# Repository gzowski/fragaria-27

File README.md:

# Fragaria-27
27 Key macropad with MX hotswap sockets, designed to fit within a iphone 13/14 pro max case giving many options given the amount of phone case options available.

* This is another project which has been possible thanks to the sponsorship from pcbway.com 

## Features
* 27 Key layout
* Per key RGB LED's
* Embedded RP2040 controller
* QMK Firmware with VIA support
* Fits into an iphone 13/14 Pro Max case
* 4 mounting screws for custom case designs

* Currently working on a one handed keyboard mode using chord

## Parts
| Part | Quantity     | Description                |
| :-------- | :------- | :------------------------- |
| Switches | 27 | MX Switches |
| Keycaps | 27 | 1U Keycaps |
| PCB Components | - | Included in kicad design and within PCB/bom/ibom.html |
## Optional Parts

| Part | Quantity     | Description                |
| :-------- | :------- | :------------------------- |
| Phone Case | 1 | iPhone 13/14 Pro Max case |

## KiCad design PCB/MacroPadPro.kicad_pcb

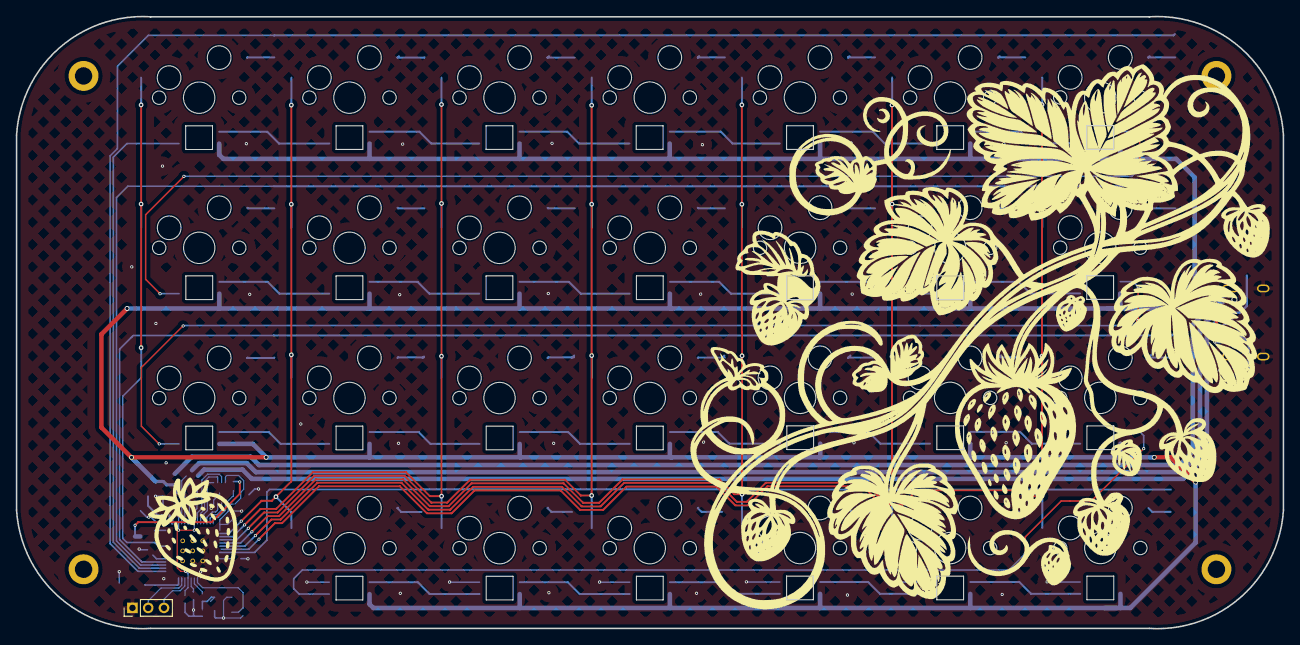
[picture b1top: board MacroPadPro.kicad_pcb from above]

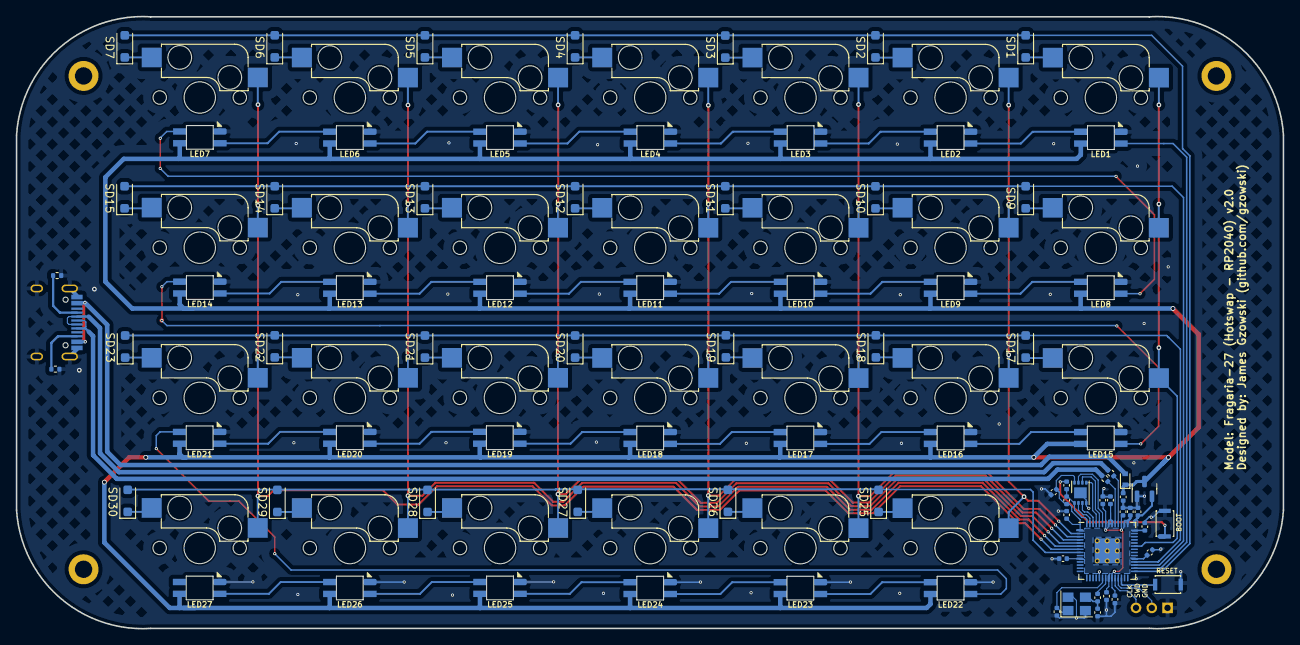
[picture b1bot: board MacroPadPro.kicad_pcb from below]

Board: 2 copper layers, 160.7 x 77.6 mm, 116 parts (84 on the bottom side), 88 nets.

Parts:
C1, C3, C4, C10: JMK105BJ105KV-F; C_0402_1005Metric
C2, C19: GJM1555C1H220JB01D; C_0402_1005Metric
C5, C6, C7, C8, C11, C13, C14, C15, C18: CC0402KRX5R5BB104; C_0402_1005Metric
D1: RB520SM-40T2R; D_SOD-523
FLASH1: w25q16jvuxiq; SON-8-1EP_3x2mm_P0.5mm_EP1.4x1.6mm
J1, J2: KXT331LHS; SW_SPST_CK_KXT3
LED1, LED2, LED3, LED4, LED5, LED6, LED7, LED8, LED9, LED10, LED11, LED12, LED13, LED14, LED15, LED16, LED17, LED18, LED19, LED20, LED21, LED22, LED23, LED24, LED25, LED26, LED27: SK6803MINI-E-001; SK6812-MINI-E
R1, R7: CRT0402AFY-1001GLF; C_0402_1005Metric
R2: CRT0402ADY-1002GLF; C_0402_1005Metric
R3, R4: CRG0402F27R; R_0402_1005Metric
R5, R6: CR0402F5K10Q10Z; R_0402_1005Metric
SD1, SD2, SD3, SD4, SD5, SD6, SD7, SD9, SD10, SD11, SD12, SD13, SD14, SD15, SD17, SD18, SD19, SD20, SD21, SD22, SD23, SD25, SD26, SD27, SD28, SD29, SD30: 1N4148W; D_SOD-123F
SW1, SW2, SW3, SW4, SW5, SW6, SW7, SW8, SW9, SW10, SW11, SW12, SW13, SW14, SW15, SW16, SW17, SW18, SW19, SW20, SW21, SW22, SW23, SW24, SW25, SW26, SW27: CPG151101S11; SW_Cherry_MX_1.00u_PCB_HOTSWAP_Details
U1: AP2210N-3.3TRG1; SOT-23
U3: RP2040; RP2040-QFN-56
USB2: TYPE-C-31-M-12; HRO-TYPE-C-31-M-12
Y1: TAXM12M4RKDCDT2T; Crystal_SMD_3225-4Pin_3.2x2.5mm
hole: hole
hole#2, hole#3, hole#4: hole
pin: DNP; PinHeader_1x03_P2.00mm_Vertical

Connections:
+1V1: C3.1, C6.1, C7.1, U3.23 (DVDD), U3.45 (VREG_VOUT), U3.50 (DVDD)
+3V3: C4.1, C5.1, C8.1, C10.1, C11.1, C13.1, C14.1, C15.1, C18.1, FLASH1.8 (VCC), R2.1, U1.2 (VO), U3.1 (IOVDD), U3.10 (IOVDD), U3.22 (IOVDD), U3.33 (IOVDD), U3.42 (IOVDD), U3.43 (ADC_AVDD), U3.44 (VREG_IN), U3.48 (USB_VDD), U3.49 (IOVDD)
/QSPI_SCLK: FLASH1.6 (CLK), U3.52 (QSPI_SCLK)
/QSPI_SD0: FLASH1.5 (DI(IO0)), U3.53 (QSPI_SD0)
/QSPI_SD1: FLASH1.2 (DO(IO1)), U3.55 (QSPI_SD1)
/QSPI_SD2: FLASH1.3 (IO2), U3.54 (QSPI_SD2)
/QSPI_SD3: FLASH1.7 (IO3), U3.51 (QSPI_SD3)
/QSPI_SS: FLASH1.1 (~CS), R1.1, R2.2, U3.56 (QSPI_SS)
/RUN: J1.1, U3.26 (RUN)
/SWCLK: U3.24 (SWCLK), pin.3
/SWD: U3.25 (SWD), pin.2
/USB_D+: R3.1, USB2.6 (DP1), USB2.8 (DP2)
/USB_D-: R4.1, USB2.5 (DN2), USB2.7 (DN1)
/~USB_BOOT: J2.1, R1.2
COL1: SW1.2, SW8.2, SW15.2, U3.37 (GPIO25)
COL2: SW2.2, SW9.2, SW16.2, SW22.2, U3.2 (GPIO0)
COL3: SW3.2, SW10.2, SW17.2, SW23.2, U3.3 (GPIO1)
COL4: SW4.2, SW11.2, SW18.2, SW24.2, U3.4 (GPIO2)
COL5: SW5.2, SW12.2, SW19.2, SW25.2, U3.5 (GPIO3)
COL6: SW6.2, SW13.2, SW20.2, SW26.2, U3.6 (GPIO4)
COL7: SW7.2, SW14.2, SW21.2, SW27.2, U3.7 (GPIO5)
GND: C1.2, C2.2, C3.2, C4.2, C5.2, C6.2, C7.2, C8.2, C10.2, C11.2, C13.2, C14.2, C15.2, C18.2, C19.2, FLASH1.4 (GND), FLASH1.9 (EP), J1.2, J2.2, LED1.3 (VSS), LED2.3 (VSS), LED3.3 (VSS), LED4.3 (VSS), LED5.3 (VSS), LED6.3 (VSS), LED7.3 (VSS), LED8.3 (VSS), LED9.3 (VSS), LED10.3 (VSS), LED11.3 (VSS), LED12.3 (VSS), LED13.3 (VSS), LED14.3 (VSS), LED15.3 (VSS), LED16.3 (VSS), LED17.3 (VSS), LED18.3 (VSS), LED19.3 (VSS), LED20.3 (VSS), LED21.3 (VSS), LED22.3 (VSS), LED23.3 (VSS), LED24.3 (VSS), LED25.3 (VSS), LED26.3 (VSS), LED27.3 (VSS), R5.1, R6.1, U1.1 (GND), U3.19 (TESTEN), U3.57 (GND), USB2.1 (GND), USB2.12 (GND), USB2.13 (SHIELD), Y1.2, Y1.4, pin.1
LED_D_IN: LED1.4 (DIN), U3.30 (GPIO19)
unnamed: LED1.2 (DOUT), LED2.4 (DIN)
unnamed: LED2.2 (DOUT), LED3.4 (DIN)
unnamed: LED3.2 (DOUT), LED4.4 (DIN)
unnamed: LED4.2 (DOUT), LED5.4 (DIN)
unnamed: LED5.2 (DOUT), LED6.4 (DIN)
unnamed: LED6.2 (DOUT), LED7.4 (DIN)
unnamed: LED7.2 (DOUT), LED8.4 (DIN)
unnamed: LED8.2 (DOUT), LED9.4 (DIN)
unnamed: LED9.2 (DOUT), LED10.4 (DIN)
unnamed: LED10.2 (DOUT), LED11.4 (DIN)
unnamed: LED11.2 (DOUT), LED12.4 (DIN)
unnamed: LED12.2 (DOUT), LED13.4 (DIN)
unnamed: LED13.2 (DOUT), LED14.4 (DIN)
unnamed: LED14.2 (DOUT), LED15.4 (DIN)
unnamed: LED15.2 (DOUT), LED16.4 (DIN)
unnamed: LED16.2 (DOUT), LED17.4 (DIN)
unnamed: LED17.2 (DOUT), LED18.4 (DIN)
unnamed: LED18.2 (DOUT), LED19.4 (DIN)
unnamed: LED19.2 (DOUT), LED20.4 (DIN)
unnamed: LED20.2 (DOUT), LED21.4 (DIN)
unnamed: LED21.2 (DOUT), LED22.4 (DIN)
unnamed: LED22.2 (DOUT), LED23.4 (DIN)
unnamed: LED23.2 (DOUT), LED24.4 (DIN)
unnamed: LED24.2 (DOUT), LED25.4 (DIN)
unnamed: LED25.2 (DOUT), LED26.4 (DIN)
unnamed: LED26.2 (DOUT), LED27.4 (DIN)
unnamed: SD1.1 (K), SW1.1
unnamed: SD2.1 (K), SW2.1
unnamed: SD3.1 (K), SW3.1
unnamed: SD4.1 (K), SW4.1
unnamed: SD5.1 (K), SW5.1
unnamed: SD6.1 (K), SW6.1
unnamed: SD7.1 (K), SW7.1
unnamed: SD9.1 (K), SW8.1
unnamed: SD10.1 (K), SW9.1
unnamed: SD11.1 (K), SW10.1
unnamed: SD12.1 (K), SW11.1
unnamed: SD13.1 (K), SW12.1
unnamed: SD14.1 (K), SW13.1
unnamed: SD15.1 (K), SW14.1
unnamed: SD17.1 (K), SW15.1
unnamed: SD18.1 (K), SW16.1
unnamed: SD19.1 (K), SW17.1
unnamed: SD20.1 (K), SW18.1
unnamed: SD21.1 (K), SW19.1
unnamed: SD22.1 (K), SW20.1
unnamed: SD23.1 (K), SW21.1
unnamed: SD25.1 (K), SW22.1
unnamed: SD26.1 (K), SW23.1
unnamed: SD27.1 (K), SW24.1
unnamed: SD28.1 (K), SW25.1
unnamed: SD29.1 (K), SW26.1
unnamed: SD30.1 (K), SW27.1
unnamed: R4.2, U3.46 (USB_DM)
unnamed: R3.2, U3.47 (USB_DP)
unnamed: C19.1, U3.20 (XIN), Y1.1
unnamed: C2.1, R7.1, R7.2, U3.21 (XOUT), Y1.3
unnamed: R5.2, USB2.4 (CC1)
unnamed: R6.2, USB2.10 (CC2)
ROW1: SD1.2 (A), SD2.2 (A), SD3.2 (A), SD4.2 (A), SD5.2 (A), SD6.2 (A), SD7.2 (A), U3.29 (GPIO18)
ROW2: SD9.2 (A), SD10.2 (A), SD11.2 (A), SD12.2 (A), SD13.2 (A), SD14.2 (A), SD15.2 (A), U3.31 (GPIO20)
ROW3: SD17.2 (A), SD18.2 (A), SD19.2 (A), SD20.2 (A), SD21.2 (A), SD22.2 (A), SD23.2 (A), U3.32 (GPIO21)
ROW4: SD25.2 (A), SD26.2 (A), SD27.2 (A), SD28.2 (A), SD29.2 (A), SD30.2 (A), U3.8 (GPIO6)
VBUS: D1.2 (A), USB2.2 (VBUS), USB2.11 (VBUS)
vsys: C1.1, D1.1 (K), LED1.1 (VDD), LED2.1 (VDD), LED3.1 (VDD), LED4.1 (VDD), LED5.1 (VDD), LED6.1 (VDD), LED7.1 (VDD), LED8.1 (VDD), LED9.1 (VDD), LED10.1 (VDD), LED11.1 (VDD), LED12.1 (VDD), LED13.1 (VDD), LED14.1 (VDD), LED15.1 (VDD), LED16.1 (VDD), LED17.1 (VDD), LED18.1 (VDD), LED19.1 (VDD), LED20.1 (VDD), LED21.1 (VDD), LED22.1 (VDD), LED23.1 (VDD), LED24.1 (VDD), LED25.1 (VDD), LED26.1 (VDD), LED27.1 (VDD), U1.3 (VI)

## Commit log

2024-10-05 First push
2024-10-06 Updated PCB and added BOM
2024-10-18 Images and Readme.MD
2024-10-18 README Changes
2024-10-19 Added QMK code
2024-10-19 Readme updated
2024-11-07 Updated PCB design to fix GND fault and update BOM components
2024-11-07 Updated BOM components, fixed with known working parts
2024-11-09 Updating firmware, one handed full keyboard options
